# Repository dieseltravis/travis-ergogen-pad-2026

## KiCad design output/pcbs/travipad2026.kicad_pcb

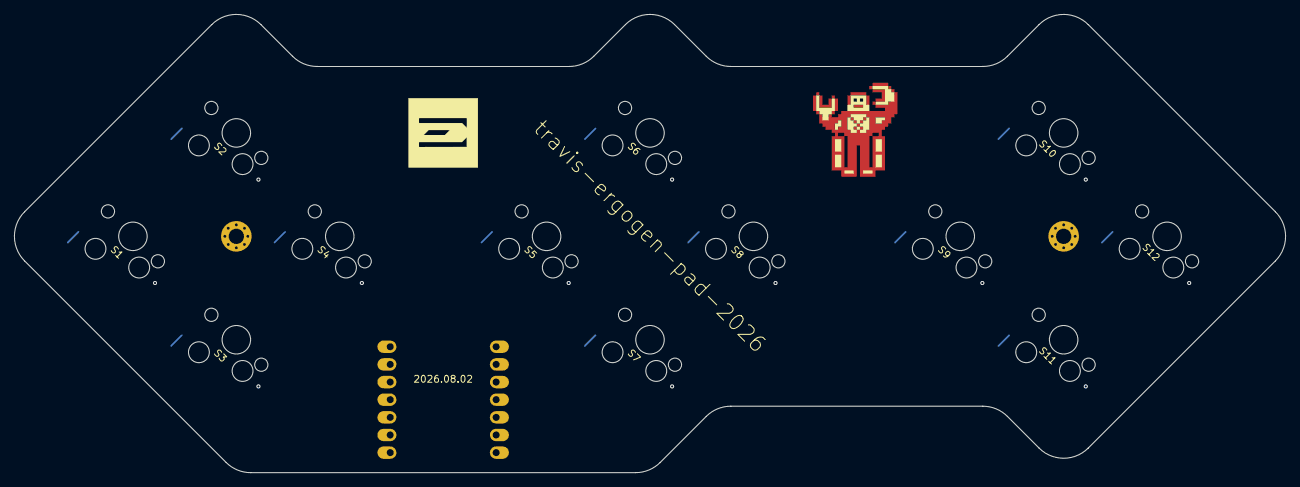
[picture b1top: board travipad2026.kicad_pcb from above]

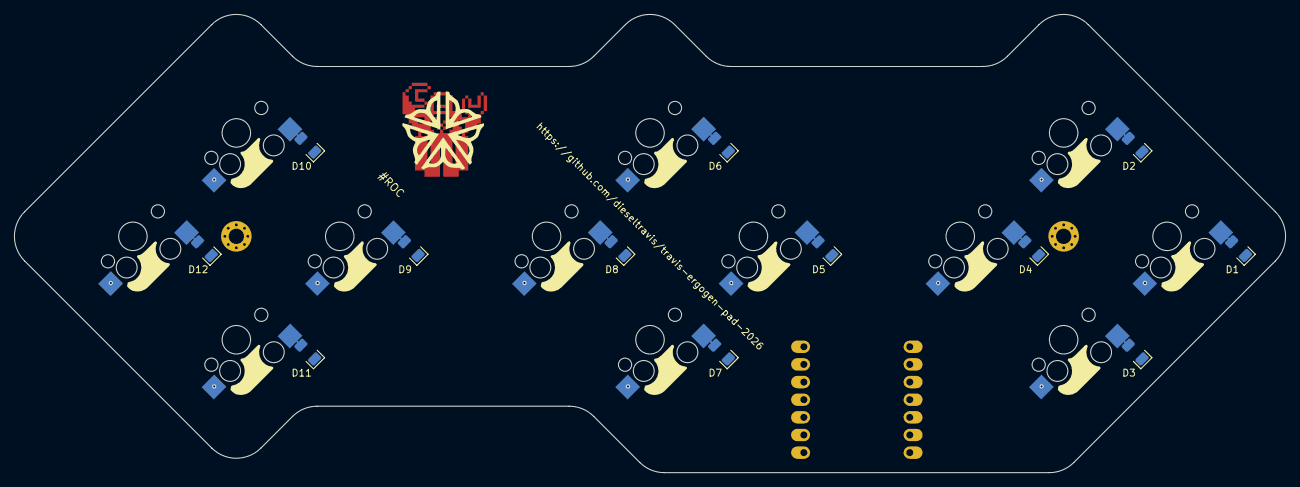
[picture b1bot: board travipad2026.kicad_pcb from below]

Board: 2 copper layers, 183.0 x 66.0 mm, 30 parts (25 on the bottom side), 19 nets.

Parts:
D1, D2, D3, D4, D5, D6, D7, D8, D9, D10, D11, D12: C7420318; D_1206_3216Metric
HOLE1, HOLE2: MountingHole_2.2mm_M2_Pad_Via
LOGO1: utility_ergogen_logo
LOGO2: travis
MCU1: XIAO-BLE
ROC1: travis
S1, S2, S3, S4, S5, S6, S7, S8, S9, S10, S11, S12: C41430893; switch_mx

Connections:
bottom_col0_row0: D1.2, S1.2
bottom_col0_row1: D2.2, S2.2
bottom_col1_row0: D3.2, S3.2
bottom_col1_row1: D4.2, S4.2
col0: MCU1.9, S1.1, S2.1, S3.1, S4.1
col1: MCU1.10, S5.1, S6.1, S7.1, S8.1
col2: MCU1.11, S9.1, S10.1, S11.1, S12.1
middle_col0_row0: D5.2, S5.2
middle_col0_row1: D6.2, S6.2
middle_col1_row0: D7.2, S7.2
middle_col1_row1: D8.2, S8.2
row0: D3.1, D7.1, D11.1, MCU1.1
row1: D1.1, D5.1, D9.1, MCU1.2
row2: D4.1, D8.1, D12.1, MCU1.3
row3: D2.1, D6.1, D10.1, MCU1.4
top_col0_row0: D9.2, S9.2
top_col0_row1: D10.2, S10.2
top_col1_row0: D11.2, S11.2
top_col1_row1: D12.2, S12.2
